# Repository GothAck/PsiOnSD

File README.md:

# PsiOnSD
## Brief
Building on the [Psioπ](https://hackaday.io/project/4042-psio) work by [RasmusB](https://hackaday.io/RasmusB), and utilizing the OSD3358 SiP,
I'm hoping to produce a drop in replacement for the Psion MX5 main board that will re-use the existing keyboard and display.

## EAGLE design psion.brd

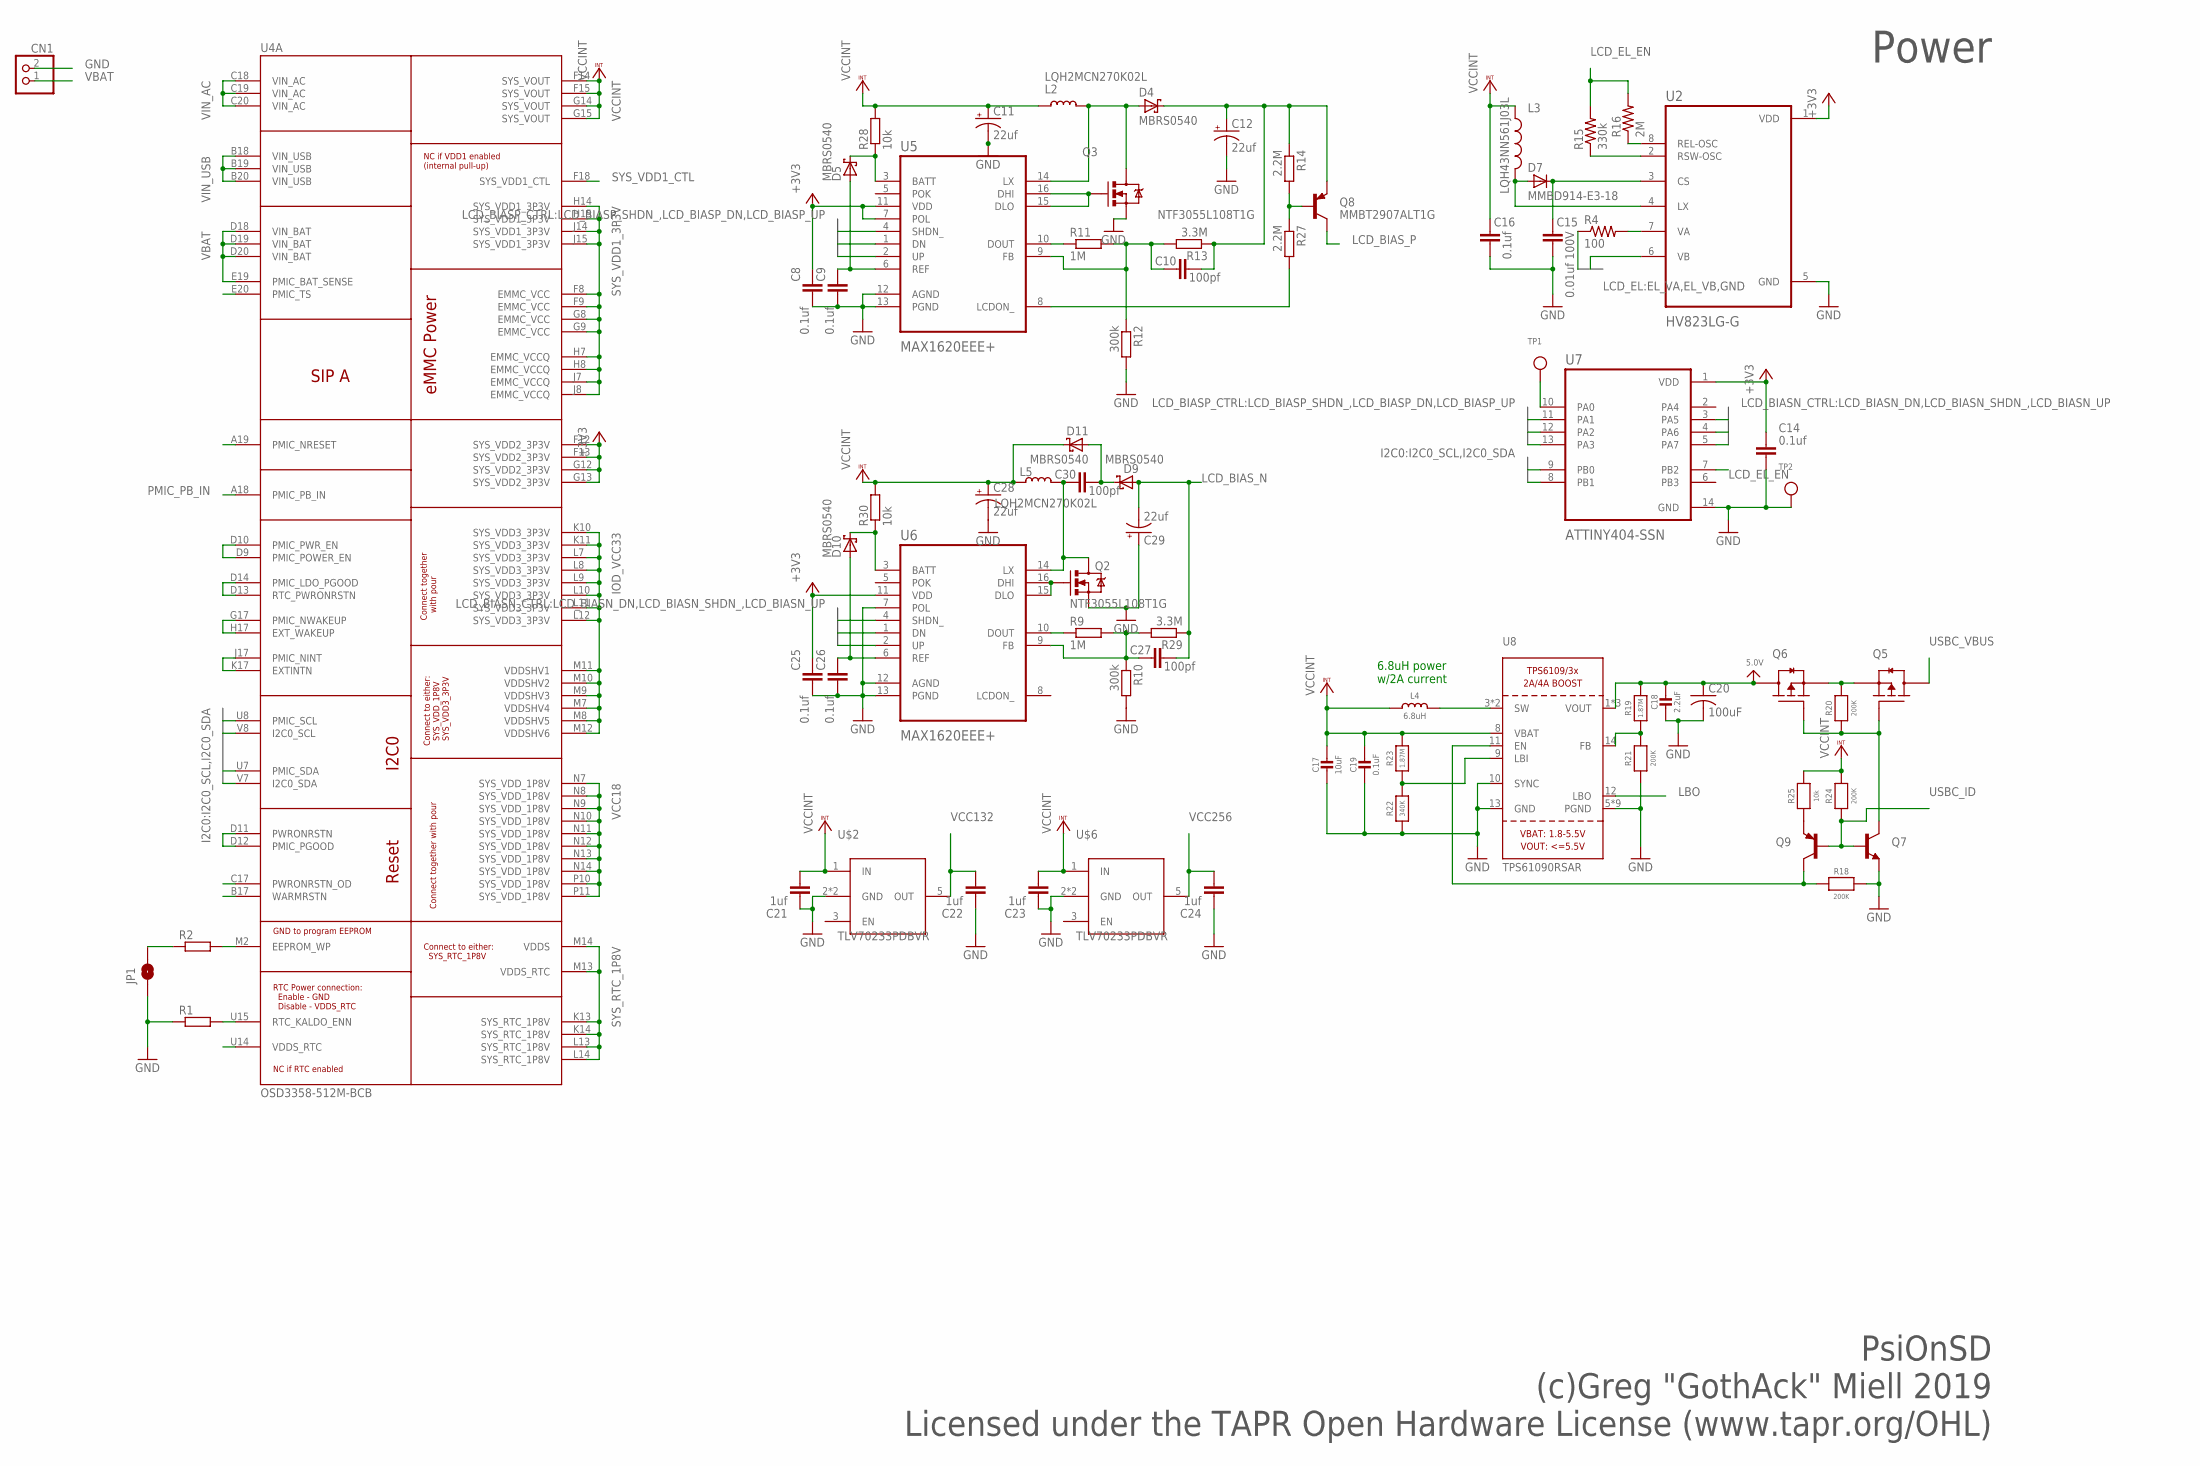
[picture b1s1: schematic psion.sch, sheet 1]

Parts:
C8, C9, C14, C16, C25, C26: 0.1uf; C805
C10, C27, C30: 100pf; C805
C11, C12, C28, C29: 22uf; CAPCP6032X280N
C15: 0.01uf 100V; C805
C17: 10uF; 0805
C18: 2.2uF; 0805
C19: 0.1uF; 0805
C20: 100uF; C1210
C21, C22, C23, C24: 1uf; C805
CN1: JST_2PIN-SMT-RA; JST-PH-2-SMT-RA
D4, D5, D9, D10, D11: MBRS0540; SOD3718X135N
D7: MMBD914-E3-18; SOT95P280X135-3N
JP1: JUMPER-SMT_2_NO_NO-SILK; SMT-JUMPER_2_NO_NO-SILK
L2, L5: LQH2MCN270K02L; INDUCTOR_1007
L3: LQH43NN561J03L; IND_LQH43CN1R0M03L
L4: 6.8uH; INDUCTOR_5X5MM_TDK_VLC5045
Q2, Q3: NTF3055L108T1G; SOT23-3
Q5, Q6: MOSFET-PCH_SOT-223; SOT230P700X160-4N
Q7: NPN_SOT-323; SOT65P210X110-3N
Q8: MMBT2907ALT1G; SOT95P280X135-3N
Q9: PNP_SOT-323; SOT65P210X110-3N
R1, R2: R-EU_R0805; R0805
R4: 100; M0805
R9, R11: 1M; R0805
R10, R12: 300k; R0805
R13, R29: 3.3M; R0805
R14, R27: 2.2M; R0805
R15: 330k; M0805
R16: 2M; M0805
R18, R20, R21, R24: 200K; 0805
R19: 1.87M; 0805
R22: 340K; _0805MP
R23: 1.87M; _0805MP
R25: 10k; 0805
R28, R30: 10k; R0805
TP1, TP2: TESTPOINTROUND1MM; TESTPOINT_ROUND_1MM
U2: HV823LG-G; SOIC127P600X175-8N
U4: OSD3358-512M-BCB; OSD335X-BGA-400
U5, U6: MAX1620EEE+; SOP63P602X175-16N
U7: ATTINY404-SSN; SOIC127P600X175-14N
U8: TPS61090RSAR; PVQFN-16
U$2, U$6: TLV70233PDBVR; SOT23-5

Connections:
5.0V: C18.1, C20.1, Q6.4 (D), R19.2, U8.1 (VOUT), U8.15 (VOUT), U8.16 (VOUT)
+3V3: C8.1, C14.1, C25.1, U2.1 (VDD), U4.F12 (SYS_VDD2_3P3V), U4.F13 (SYS_VDD2_3P3V), U4.G12 (SYS_VDD2_3P3V), U4.G13 (SYS_VDD2_3P3V), U5.7 (POL), U5.11 (VDD), U6.11 (VDD), U7.1 (VDD); also elsewhere on the board
BOOST_EN: Q9.3 (C), R18.1, U8.11 (EN)
EL_VA: R4.1; also elsewhere on the board
EL_VA_PRE: R4.2, U2.7 (VA)
EL_VB: U2.6 (VB); also elsewhere on the board
GND: C8.2, C9.2, C11.N (-), C12.N (-), C14.2, C15.2, C16.2, C17.2, C18.2, C19.2, C20.2, C21.1, C22.1, C23.1, C24.1, C25.2, C26.2, C28.N (-), C29.P (+), CN1.2 (1), JP1.1, Q2.2 (S), Q3.2 (S), Q7.2 (E), R1.1, R10.2, R12.2, R18.2, R21.1, R22.1, TP2.P$1, U2.5 (GND), U5.12 (AGND), U5.13 (PGND), U6.7 (POL), U6.12 (AGND), U6.13 (PGND), U7.14 (GND), U8.5 (PGND), U8.6 (PGND), U8.7 (PGND), U8.10 (SYNC), U8.13 (GND), U8.P$18 (PGND), U8.P$19 (PGND), U8.P$20 (PGND), U8.P$21 (PGND), U8.P$22 (PGND), U8.THERMAL (PGND), U$2.2 (GND), U$2.4 (GND), U$6.2 (GND), U$6.4 (GND); also elsewhere on the board
I2C0_SCL: U4.U8 (PMIC_SCL), U4.V8 (I2C0_SCL), U7.9 (PB0); also elsewhere on the board
I2C0_SDA: U4.U7 (PMIC_SDA), U4.V7 (I2C0_SDA), U7.8 (PB1); also elsewhere on the board
IOD_VCC33: U4.K10 (SYS_VDD3_3P3V), U4.K11 (SYS_VDD3_3P3V), U4.L7 (SYS_VDD3_3P3V), U4.L8 (SYS_VDD3_3P3V), U4.L9 (SYS_VDD3_3P3V), U4.L10 (SYS_VDD3_3P3V), U4.L11 (SYS_VDD3_3P3V), U4.L12 (SYS_VDD3_3P3V), U4.M7 (VDDSHV4), U4.M8 (VDDSHV5), U4.M9 (VDDSHV3), U4.M10 (VDDSHV2), U4.M11 (VDDSHV1), U4.M12 (VDDSHV6)
LBO: U8.12 (LBO)
LCD_BIASND_N: U6.1 (DN), U7.3 (PA5)
LCD_BIASN_SHDN_: U6.4 (SHDN_), U7.5 (PA7)
LCD_BIASN_UP: U6.2 (UP), U7.4 (PA6)
LCD_BIASPD_N: U5.1 (DN), U7.12 (PA2)
LCD_BIASP_SHDN_: U5.4 (SHDN_), U7.13 (PA3)
LCD_BIASP_UP: U5.2 (UP), U7.11 (PA1)
LCD_BIAS_N: C27.2, C29.N (-), D9.A, R29.1; also elsewhere on the board
LCD_BIAS_N_P1: C30.1, L5.P$2 (2), Q2.3 (D), U6.14 (LX)
LCD_BIAS_N_P2: C30.2, D9.K, D11.A
LCD_BIAS_P: Q8.3 (C); also elsewhere on the board
LCD_BIAS_P_P1: D4.A, L2.P$2 (2), Q3.3 (D), U5.14 (LX)
LCD_BIAS_P_P2: C10.2, C12.P (+), D4.K, Q8.2 (E), R13.1, R14.1
LCD_EL_EN: R15.2, R16.2, U7.7 (PB2)
unnamed: D7.1 (A), L3.2, U2.4 (LX)
unnamed: C15.1, D7.3 (K), U2.3 (CS)
unnamed: R2.2, U4.M2 (EEPROM_WP)
unnamed: U4.D9 (PMIC_POWER_EN), U4.D10 (PMIC_PWR_EN)
unnamed: U4.D13 (RTC_PWRONRSTN), U4.D14 (PMIC_LDO_PGOOD)
unnamed: U4.J17 (PMIC_NINT), U4.K17 (EXTINTN)
unnamed: U4.G17 (PMIC_NWAKEUP), U4.H17 (EXT_WAKEUP)
unnamed: U4.D11 (PWRONRSTN), U4.D12 (PMIC_PGOOD)
unnamed: JP1.2, R2.1
unnamed: Q3.1 (G), U5.15 (DLO), U5.16 (DHI)
unnamed: Q2.1 (G), U6.15 (DLO), U6.16 (DHI)
unnamed: R11.1, U5.10 (DOUT)
unnamed: C10.1, R11.2, R12.1, R13.2, U5.9 (FB)
unnamed: Q8.1 (B), R14.2, R27.1
unnamed: TP1.P$1, U7.10 (PA0)
unnamed: R27.2, U5.8 (LCDON_)
unnamed: R15.1, U2.2 (RSW-OSC)
unnamed: R16.1, U2.8 (REL-OSC)
unnamed: R22.2, R23.1, U8.9 (LBI)
unnamed: R19.1, R21.2, U8.14 (FB)
unnamed: Q5.1 (G), Q6.1 (G), Q7.3 (C), R20.1
unnamed: Q9.2 (E), R25.1
unnamed: D5.K, R28.1, U5.3 (BATT)
unnamed: C9.1, D5.A, U5.6 (REF)
unnamed: R9.1, U6.10 (DOUT)
unnamed: C27.1, R9.2, R10.1, R29.2, U6.9 (FB)
unnamed: D10.K, R30.1, U6.3 (BATT)
unnamed: C26.1, D10.A, U6.6 (REF)
PMIC_NRESET: U4.A19 (PMIC_NRESET)
PMIC_PB_IN: U4.A18 (PMIC_PB_IN); also elsewhere on the board
PMIC_TS: U4.E20 (PMIC_TS)
PWRONRSTN_OD: U4.C17 (PWRONRSTN_OD)
ROPU: R1.2, U4.U15 (RTC_KALDO_ENN)
SYS_RTC_1P8V: U4.K13 (SYS_RTC_1P8V), U4.K14 (SYS_RTC_1P8V), U4.L13 (SYS_RTC_1P8V), U4.L14 (SYS_RTC_1P8V), U4.M13 (VDDS_RTC), U4.M14 (VDDS)
SYS_VDD1_3P3V: U4.F8 (EMMC_VCC), U4.F9 (EMMC_VCC), U4.G8 (EMMC_VCC), U4.G9 (EMMC_VCC), U4.H7 (EMMC_VCCQ), U4.H8 (EMMC_VCCQ), U4.H14 (SYS_VDD1_3P3V), U4.H15 (SYS_VDD1_3P3V), U4.J7 (EMMC_VCCQ), U4.J8 (EMMC_VCCQ), U4.J14 (SYS_VDD1_3P3V), U4.J15 (SYS_VDD1_3P3V)
SYS_VDD1_CTL: U4.F18 (SYS_VDD1_CTL)
USBC_ID: Q7.1 (B), Q9.1 (B), R24.1; also elsewhere on the board
USBC_IND_SW: L4.P$2 (2), U8.3 (SW), U8.4 (SW)
USBC_VBUS: Q5.4 (D); also elsewhere on the board
USBC_VBUS_SW: Q5.3 (S), Q6.3 (S), R20.2
VBAT: CN1.1 (2), U4.D18 (VIN_BAT), U4.D19 (VIN_BAT), U4.D20 (VIN_BAT), U4.E19 (PMIC_BAT_SENSE); also elsewhere on the board
VCC18: U4.N7 (SYS_VDD_1P8V), U4.N8 (SYS_VDD_1P8V), U4.N9 (SYS_VDD_1P8V), U4.N10 (SYS_VDD_1P8V), U4.N11 (SYS_VDD_1P8V), U4.N12 (SYS_VDD_1P8V), U4.N13 (SYS_VDD_1P8V), U4.N14 (SYS_VDD_1P8V), U4.P10 (SYS_VDD_1P8V), U4.P11 (SYS_VDD_1P8V)
VCC132: C22.2, U$2.5 (OUT); also elsewhere on the board
VCC256: C24.2, U$6.5 (OUT); also elsewhere on the board
VCCINT: C11.P (+), C16.1, C17.1, C19.1, C21.2, C23.2, C28.P (+), D11.K, L2.P$1 (1), L3.1, L4.P$1 (1), L5.P$1 (1), R23.2, R24.2, R25.2, R28.2, R30.2, U4.F14 (SYS_VOUT), U4.F15 (SYS_VOUT), U4.G14 (SYS_VOUT), U4.G15 (SYS_VOUT), U8.8 (VBAT), U$2.1 (IN), U$6.1 (IN); also elsewhere on the board
VDDS_RTC@2: U4.U14 (VDDS_RTC)
VIN_AC: U4.C18 (VIN_AC), U4.C19 (VIN_AC), U4.C20 (VIN_AC)
VIN_USB: U4.B18 (VIN_USB), U4.B19 (VIN_USB), U4.B20 (VIN_USB)
WARMRSTN: U4.B17 (WARMRSTN)

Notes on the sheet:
PsiOnSD (c)Greg "GothAck" Miell 2019 Licensed under the TAPR Open Hardware License (www.tapr.org/OHL)
Power
6.8uH power w/2A current

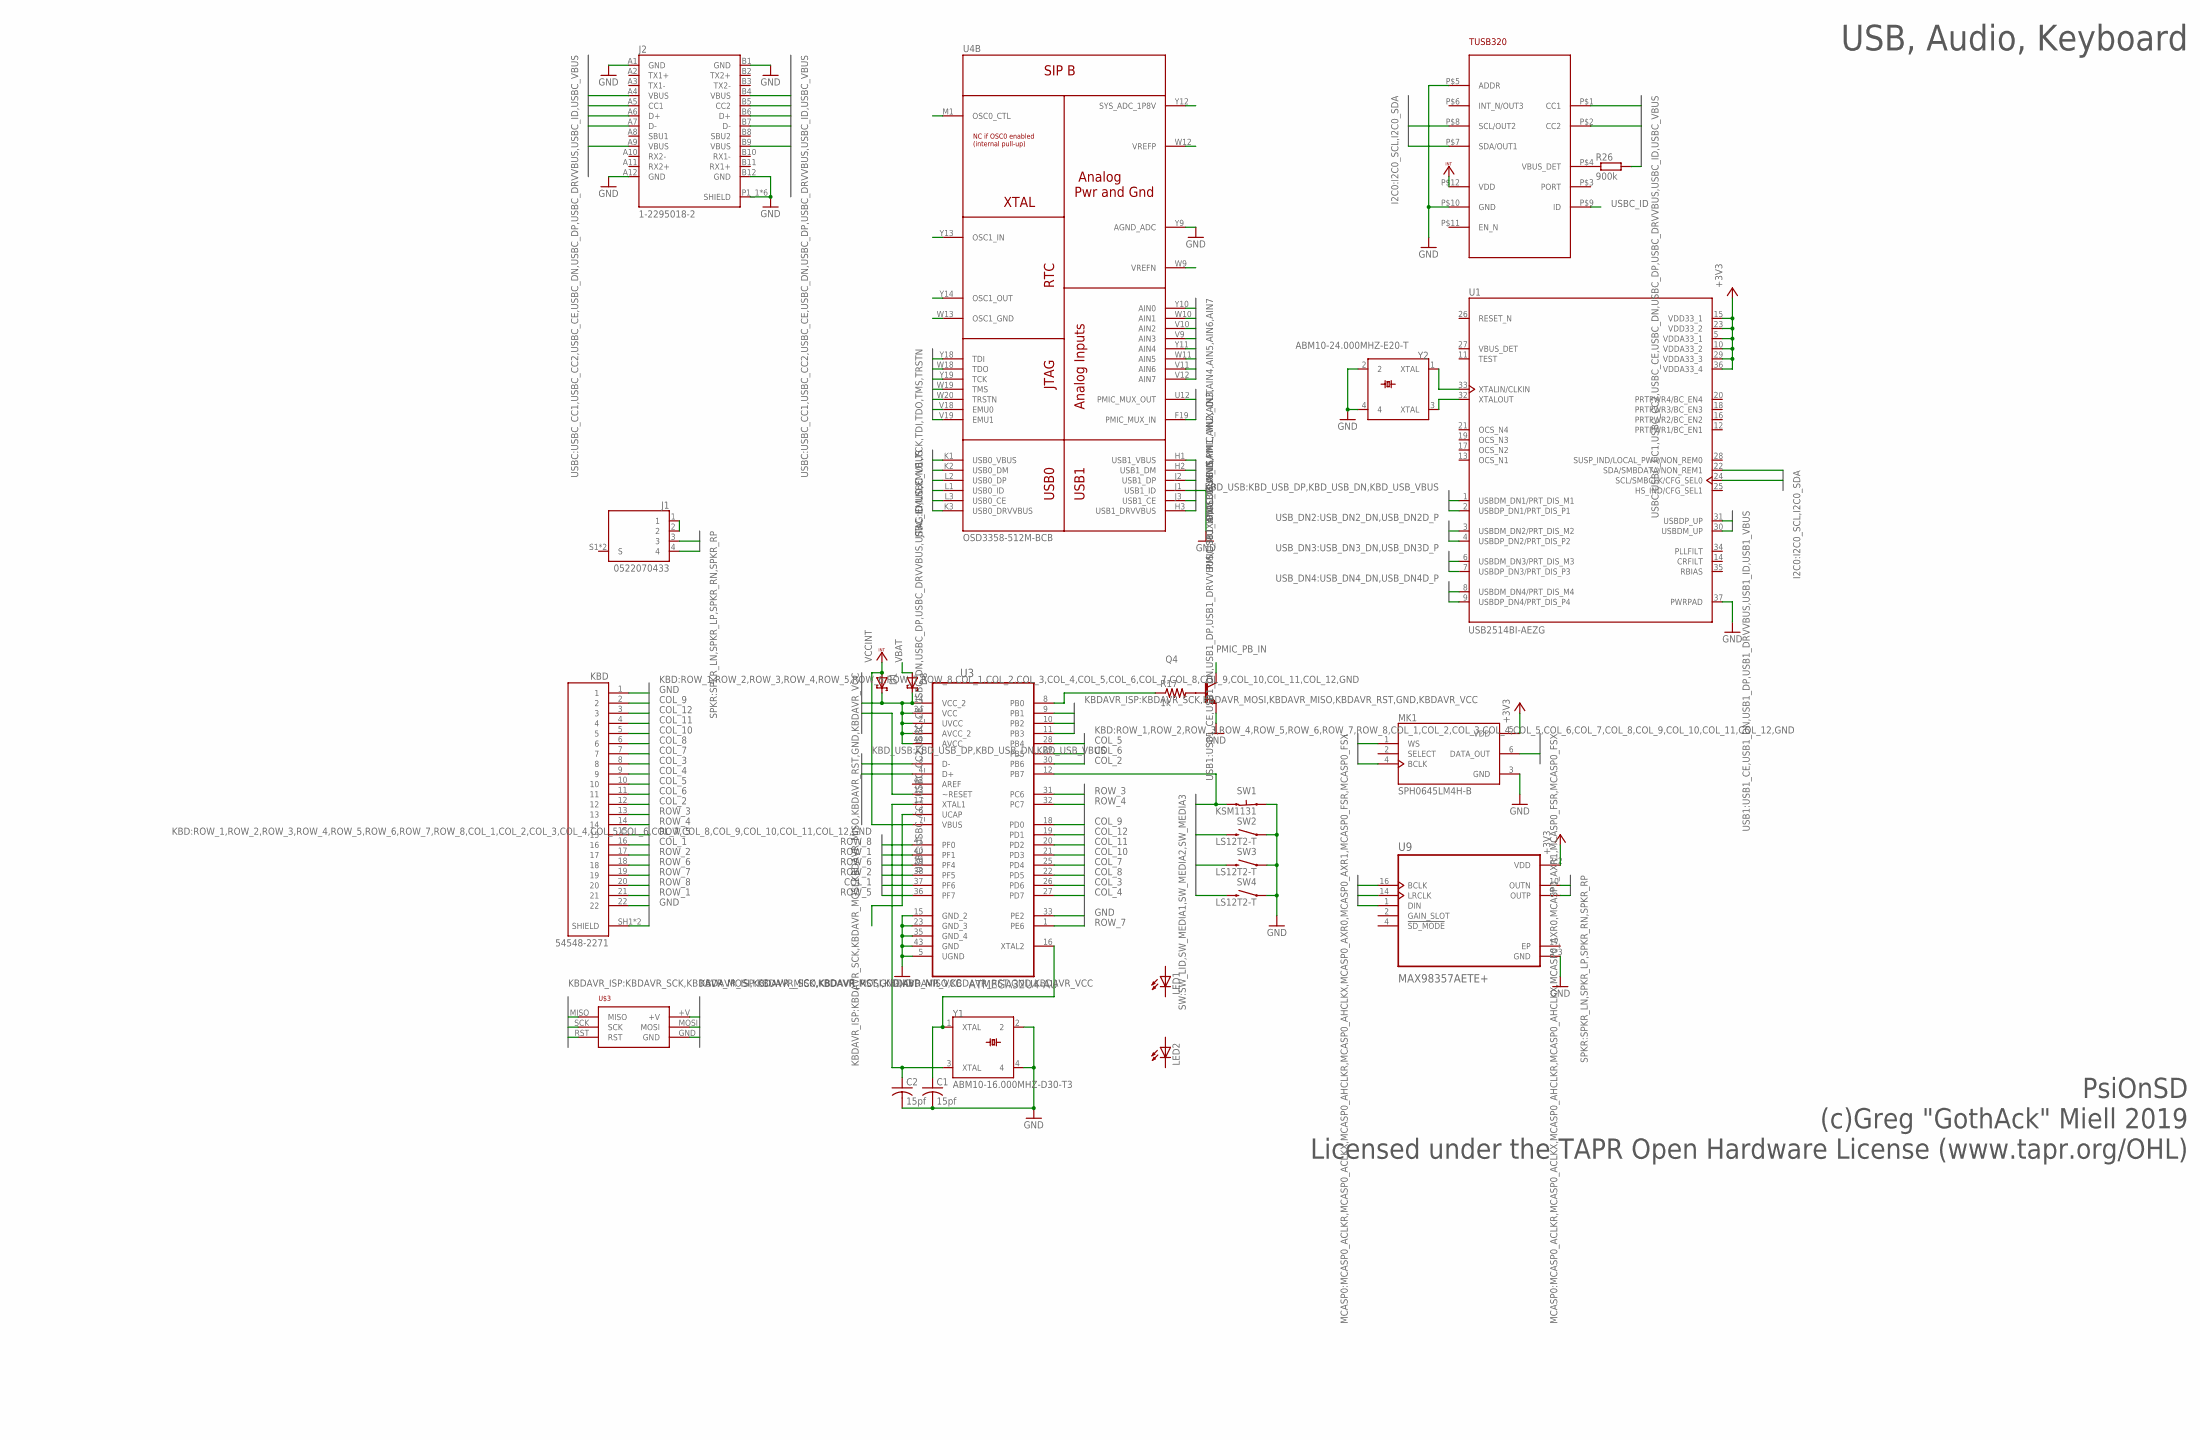
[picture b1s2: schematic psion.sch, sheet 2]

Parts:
C1, C2: 15pf; C0402
D1, D8: SCHOTTKY_SOD-123; SOD3718X135N
J1: 0522070433; MOLEX_0522070433
J2: 1-2295018-2; TE_1-2295018-2
KBD: 54548-2271; MOLEX_54548-2271
LED1, LED2: LEDCHIP-LED0805; CHIP-LED0805
MK1: SPH0645LM4H-B; MIC_SPH0645LM4H-B
Q4: NPN_SOT-323; SOT65P210X110-3N
R17: 1k; M0805
R26: 900k; R0805
SW1: KSM1131
SW2, SW3, SW4: LS12T2-T
U1: USB2514BI-AEZG; QFN50P600X600X100-37N
U3: ATMEGA32U4-AU; QFP80P1200X1200X120-44N
U4: OSD3358-512M-BCB; OSD335X-BGA-400
U9: MAX98357AETE+; QFN50P300X300X80-17N
U$3: 1.27MM-ICSP
U$4: TUSB320XQFN; X2QFN
Y1: ABM10-16.000MHZ-D30-T3; XTAL250X200X50
Y2: ABM10-24.000MHZ-E20-T; XTAL250X200X50

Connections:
+3V3: MK1.5 (VDD), U1.5 (VDDA33_1), U1.10 (VDDA33_2), U1.15 (VDD33_1), U1.23 (VDD33_2), U1.29 (VDDA33_3), U1.36 (VDDA33_4), U9.7 (VDD), U9.8 (VDD); also elsewhere on the board
AIN0: U4.Y10 (AIN0)
AIN1: U4.W10 (AIN1)
AIN2: U4.V10 (AIN2)
AIN3: U4.V9 (AIN3)
AIN4: U4.Y11 (AIN4)
AIN5: U4.W11 (AIN5)
AIN6: U4.V11 (AIN6)
AIN7: U4.V12 (AIN7)
COL_1: KBD.16, U3.37 (PF6)
COL_2: KBD.12, U3.30 (PB6)
COL_3: KBD.8, U3.26 (PD6)
COL_4: KBD.9, U3.27 (PD7)
COL_5: KBD.10, U3.28 (PB4)
COL_6: KBD.11, U3.29 (PB5)
COL_7: KBD.7, U3.25 (PD4)
COL_8: KBD.6, U3.22 (PD5)
COL_9: KBD.2, U3.18 (PD0)
COL_10: KBD.5, U3.21 (PD3)
COL_11: KBD.4, U3.20 (PD2)
COL_12: KBD.3, U3.19 (PD1)
EMU0: U4.V18 (EMU0)
EMU1: U4.V19 (EMU1)
EP: U9.17 (EP)
GND: C1.2, C2.2, J2.A1 (GND), J2.A12 (GND), J2.B1 (GND), J2.B12 (GND), J2.P1_1 (SHIELD), J2.P1_2 (SHIELD), J2.P2_1 (SHIELD), J2.P2_2 (SHIELD), J2.P4 (SHIELD), J2.P5 (SHIELD), KBD.1, KBD.22, KBD.SH1 (SHIELD), KBD.SH2 (SHIELD), MK1.3 (GND), Q4.2 (E), SW1.1, SW2.1, SW3.1, SW4.1, U1.37 (PWRPAD), U3.5 (UGND), U3.15 (GND_2), U3.23 (GND_3), U3.33 (PE2), U3.35 (GND_4), U3.43 (GND), U4.J1 (USB1_ID), U4.Y9 (AGND_ADC), U9.3 (GND), U9.11 (GND), U9.15 (GND), U$3.GND, U$4.P$5 (ADDR), U$4.P$10 (GND), Y1.2, Y1.4, Y2.2, Y2.4; also elsewhere on the board
I2C0_SCL: U1.24 (SCL/SMBCLK/CFG_SEL0), U$4.P$8 (SCL/OUT2); also elsewhere on the board
I2C0_SDA: U1.22 (SDA/SMBDATA/NON_REM1), U$4.P$7 (SDA/OUT1); also elsewhere on the board
KBDAVR_MISO: U3.11 (PB3), U$3.MISO
KBDAVR_MOSI: U3.10 (PB2), U$3.MOSI
KBDAVR_RST: U3.13 (~RESET), U$3.RST
KBDAVR_SCK: U3.9 (PB1), U$3.SCK
KBDAVR_VCC: D1.K, D8.K, U3.2 (UVCC), U3.14 (VCC_2), U3.24 (AVCC_2), U3.34 (VCC), U3.44 (AVCC), U$3.+V
KBD_USBD_N: U1.1 (USBDM_DN1/PRT_DIS_M1), U3.3 (D-)
KBD_USBD_P: U1.2 (USBDP_DN1/PRT_DIS_P1), U3.4 (D+)
MCASP0_ACLKR: MK1.4 (BCLK); also elsewhere on the board
MCASP0_ACLKX: U9.16 (BCLK); also elsewhere on the board
MCASP0_AXR0: U9.1 (DIN); also elsewhere on the board
MCASP0_AXR1: MK1.6 (DATA_OUT); also elsewhere on the board
MCASP0_FSR: MK1.1 (WS); also elsewhere on the board
MCASP0_FSX: U9.14 (LRCLK); also elsewhere on the board
unnamed: U1.33 (XTALIN/CLKIN), Y2.1 (XTAL)
unnamed: C1.1, U3.16 (XTAL2), Y1.1 (XTAL)
unnamed: C2.1, U3.17 (XTAL1), Y1.3 (XTAL)
unnamed: U1.32 (XTALOUT), Y2.3 (XTAL)
unnamed: J1.1, J1.2
unnamed: R17.1, U3.8 (PB0)
unnamed: Q4.1 (B), R17.2
unnamed: R26.1, U$4.P$4 (VBUS_DET)
OSC0_CTL: U4.M1 (OSC0_CTL)
OSC1_GND: U4.W13 (OSC1_GND)
OSC1_IN: U4.Y13 (OSC1_IN)
OSC1_OUT: U4.Y14 (OSC1_OUT)
PMIC_MUX_IN: U4.F19 (PMIC_MUX_IN)
PMIC_MUX_OUT: U4.U12 (PMIC_MUX_OUT)
PMIC_PB_IN: Q4.3 (C); also elsewhere on the board
ROW_1: KBD.21, U3.40 (PF1)
ROW_2: KBD.17, U3.38 (PF5)
ROW_3: KBD.13, U3.31 (PC6)
ROW_4: KBD.14, U3.32 (PC7)
ROW_5: KBD.15, U3.36 (PF7)
ROW_6: KBD.18, U3.39 (PF4)
ROW_7: KBD.19, U3.1 (PE6)
ROW_8: KBD.20, U3.41 (PF0)
S: J1.S1 (S), J1.S2 (S)
SPKR_LN: J1.3, U9.10 (OUTN)
SPKR_LP: J1.4, U9.9 (OUTP)
SW_LID: SW1.2, U3.12 (PB7)
SW_MEDIA1: SW2.2
SW_MEDIA2: SW3.2
SW_MEDIA3: SW4.2
SYS_ADC_1P8V: U4.Y12 (SYS_ADC_1P8V)
TCK: U4.Y19 (TCK)
TDI: U4.Y18 (TDI)
TDO: U4.W18 (TDO)
TMS: U4.W19 (TMS)
TRSTN: U4.W20 (TRSTN)
USB1D_N: U1.30 (USBDM_UP), U4.H2 (USB1_DM)
USB1D_P: U1.31 (USBDP_UP), U4.J2 (USB1_DP)
USB1_CE: U4.J3 (USB1_CE)
USB1_DRVVBUS: U4.H3 (USB1_DRVVBUS)
USB1_VBUS: U4.H1 (USB1_VBUS)
USBCD_N: J2.A7 (D-), J2.B7 (D-), U4.K2 (USB0_DM)
USBCD_P: J2.A6 (D+), J2.B6 (D+), U4.L2 (USB0_DP)
USBC_CC1: J2.A5 (CC1), U$4.P$1 (CC1)
USBC_CC2: J2.B5 (CC2), U$4.P$2 (CC2)
USBC_CE: U4.L3 (USB0_CE)
USBC_DRVVBUS: U4.K3 (USB0_DRVVBUS)
USBC_ID: U4.L1 (USB0_ID), U$4.P$9 (ID); also elsewhere on the board
USBC_VBUS: J2.A4 (VBUS), J2.A9 (VBUS), J2.B4 (VBUS), J2.B9 (VBUS), R26.2, U4.K1 (USB0_VBUS); also elsewhere on the board
USB_DN2D_N: U1.3 (USBDM_DN2/PRT_DIS_M2)
USB_DN2D_P: U1.4 (USBDP_DN2/PRT_DIS_P2)
USB_DN3D_N: U1.6 (USBDM_DN3/PRT_DIS_M3)
USB_DN3D_P: U1.7 (USBDP_DN3/PRT_DIS_P3)
USB_DN4D_N: U1.8 (USBDM_DN4/PRT_DIS_M4)
USB_DN4D_P: U1.9 (USBDP_DN4/PRT_DIS_P4)
VBAT: D8.A; also elsewhere on the board
VCCINT: D1.A, U3.7 (VBUS), U$4.P$12 (VDD); also elsewhere on the board
VREFN: U4.W9 (VREFN)
VREFP: U4.W12 (VREFP)

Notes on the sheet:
PsiOnSD (c)Greg "GothAck" Miell 2019 Licensed under the TAPR Open Hardware License (www.tapr.org/OHL)
USB, Audio, Keyboard

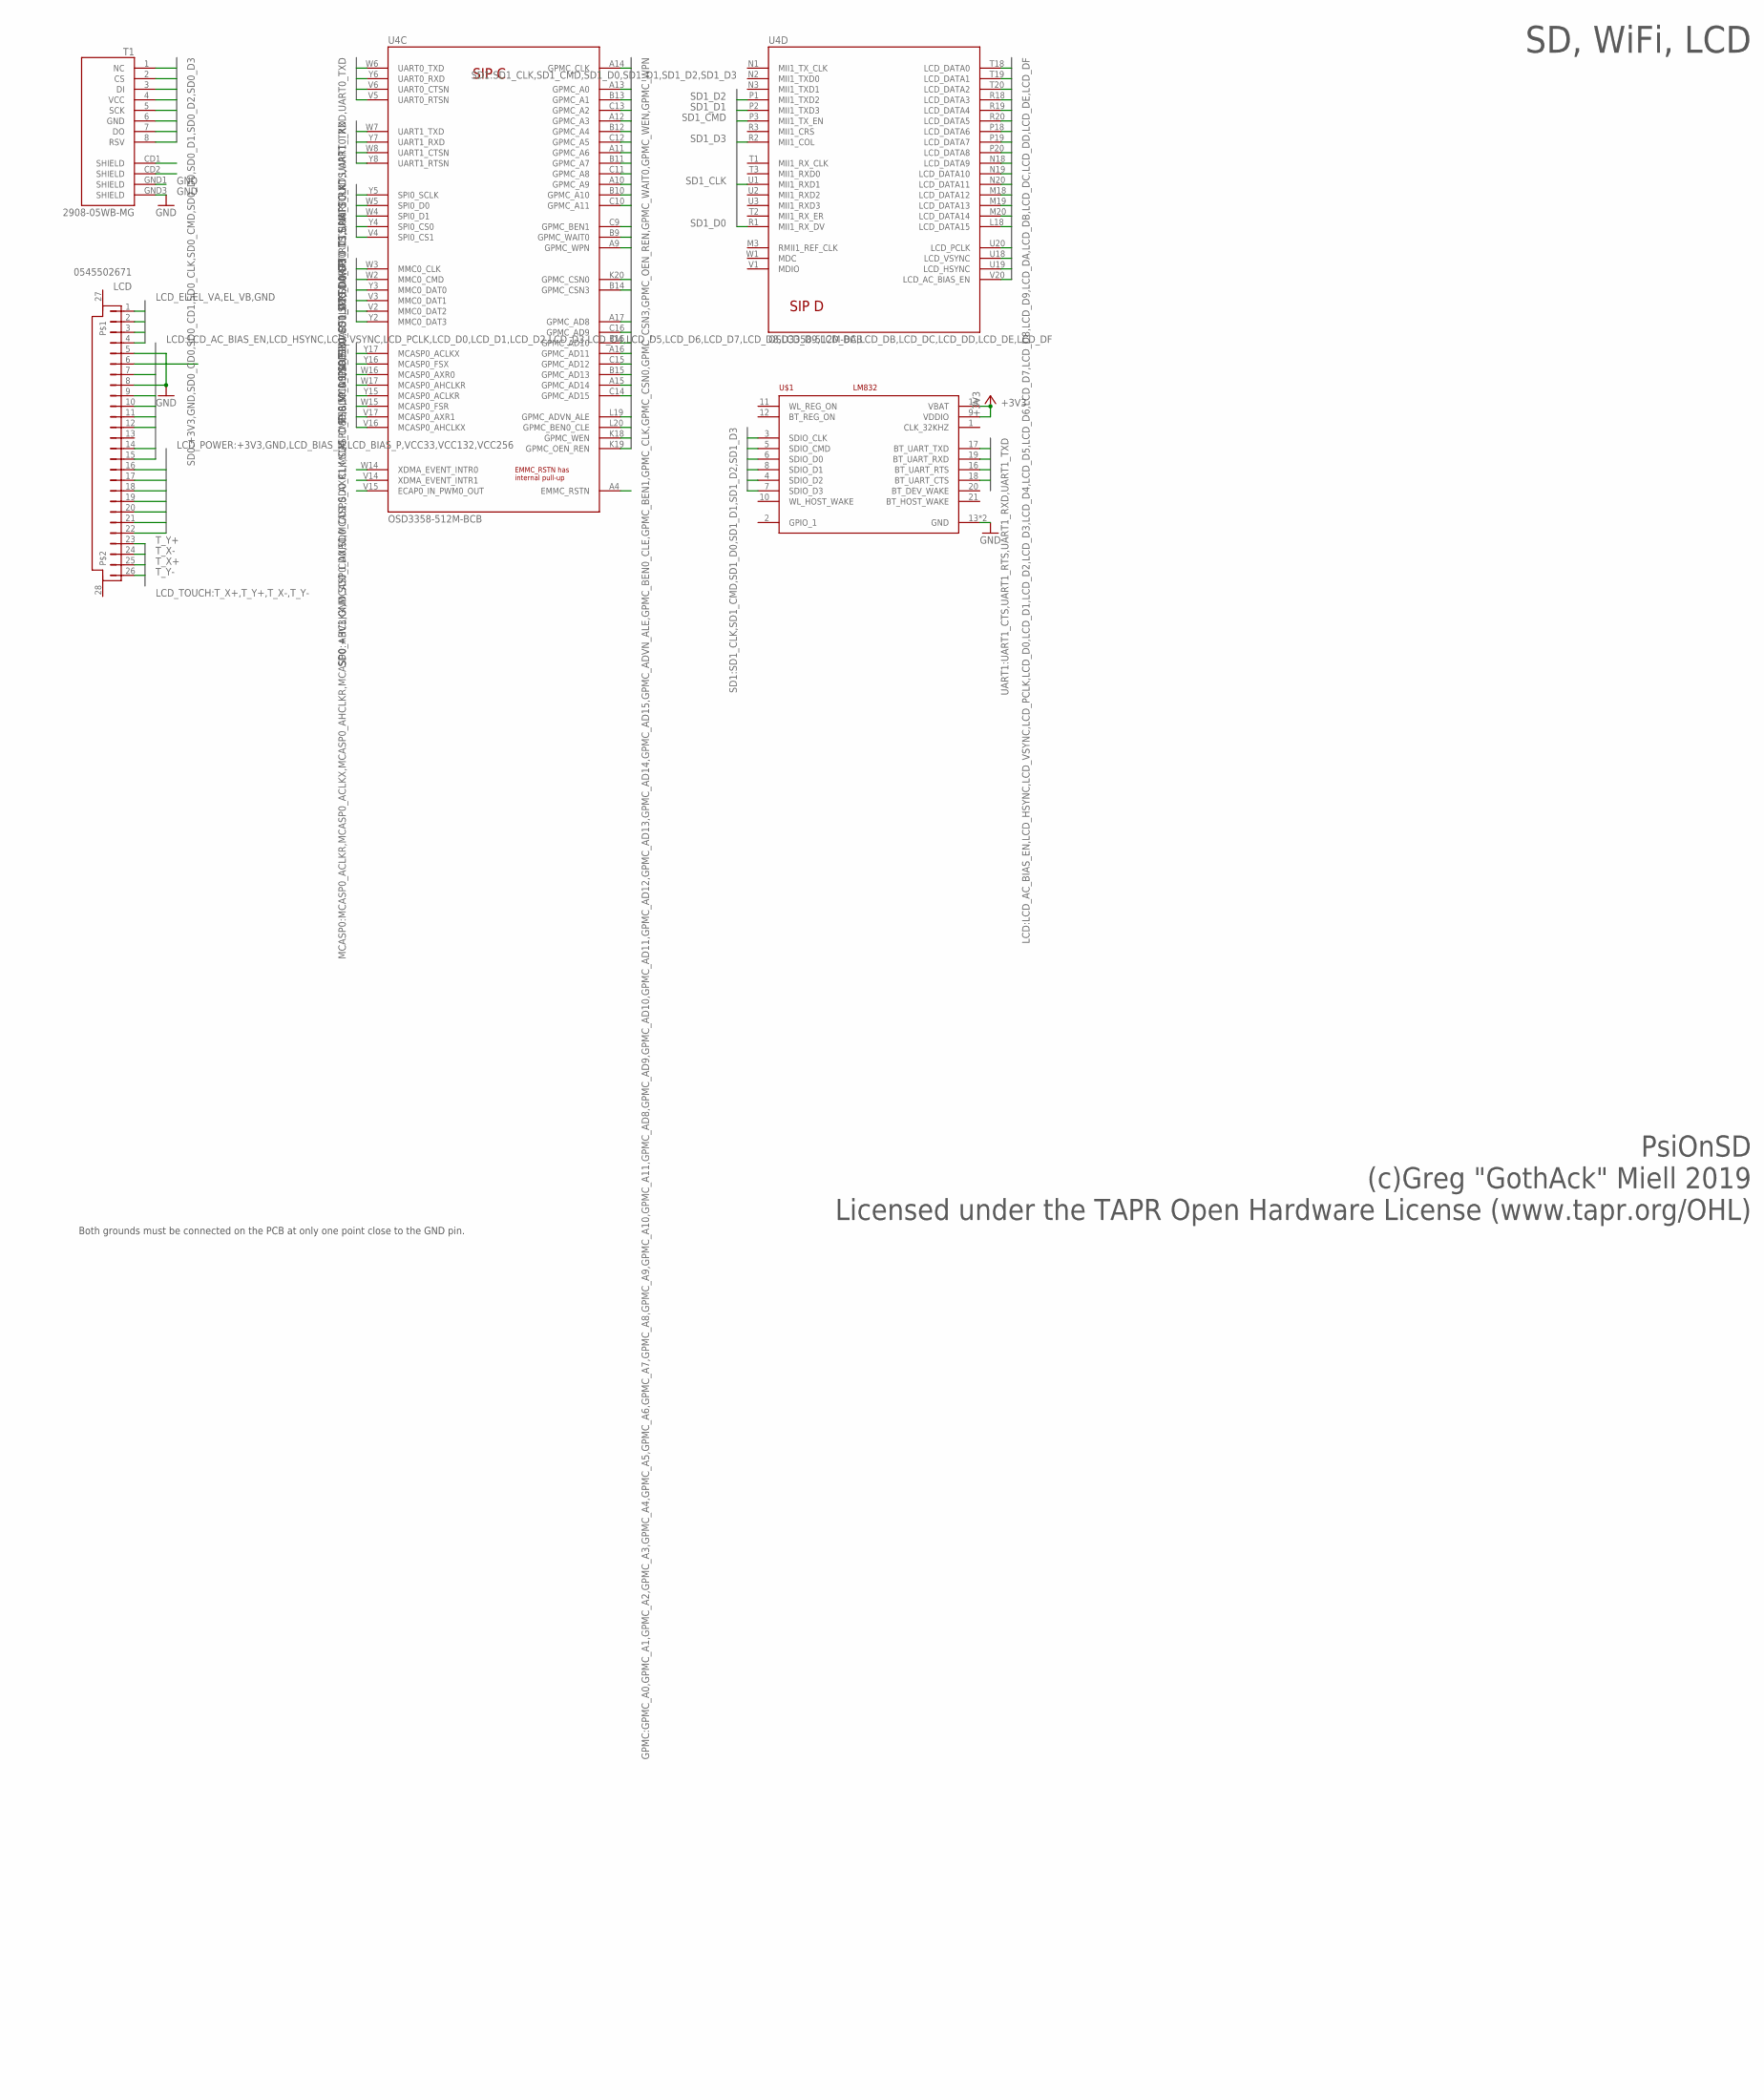
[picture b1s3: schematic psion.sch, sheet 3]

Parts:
LCD: 0545502671
T1: 2908-05WB-MG; MICRO-SD-SOCKET-PP
U4: OSD3358-512M-BCB; OSD335X-BGA-400
U$1: LM832EMBEDDED; LM832SMT_EMB

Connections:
+3V3: LCD.16, LCD.21, T1.4 (VCC), U$1.9 (VDDIO), U$1.14 (VBAT); also elsewhere on the board
ECAP0_IN_PWM0_OUT: U4.V15 (ECAP0_IN_PWM0_OUT)
EL_VA: LCD.3; also elsewhere on the board
EL_VB: LCD.1; also elsewhere on the board
EMMC_RSTN: U4.A4 (EMMC_RSTN)
GND: LCD.2, LCD.4, LCD.5, LCD.8, LCD.22, T1.6 (GND), T1.GND1 (SHIELD), T1.GND3 (SHIELD), U$1.13 (GND), U$1.15 (GND); also elsewhere on the board
GPMC_A0: U4.A13 (GPMC_A0)
GPMC_A1: U4.B13 (GPMC_A1)
GPMC_A2: U4.C13 (GPMC_A2)
GPMC_A3: U4.A12 (GPMC_A3)
GPMC_A4: U4.B12 (GPMC_A4)
GPMC_A5: U4.C12 (GPMC_A5)
GPMC_A6: U4.A11 (GPMC_A6)
GPMC_A7: U4.B11 (GPMC_A7)
GPMC_A8: U4.C11 (GPMC_A8)
GPMC_A9: U4.A10 (GPMC_A9)
GPMC_A10: U4.B10 (GPMC_A10)
GPMC_A11: U4.C10 (GPMC_A11)
GPMC_AD8: U4.A17 (GPMC_AD8)
GPMC_AD9: U4.C16 (GPMC_AD9)
GPMC_AD10: U4.B16 (GPMC_AD10)
GPMC_AD11: U4.A16 (GPMC_AD11)
GPMC_AD12: U4.C15 (GPMC_AD12)
GPMC_AD13: U4.B15 (GPMC_AD13)
GPMC_AD14: U4.A15 (GPMC_AD14)
GPMC_AD15: U4.C14 (GPMC_AD15)
GPMC_ADVN_ALE: U4.L19 (GPMC_ADVN_ALE)
GPMC_BEN0_CLE: U4.L20 (GPMC_BEN0_CLE)
GPMC_BEN1: U4.C9 (GPMC_BEN1)
GPMC_CLK: U4.A14 (GPMC_CLK)
GPMC_CSN0: U4.K20 (GPMC_CSN0)
GPMC_CSN3: U4.B14 (GPMC_CSN3)
GPMC_OEN_REN: U4.K19 (GPMC_OEN_REN)
GPMC_WAIT0: U4.B9 (GPMC_WAIT0)
GPMC_WEN: U4.K18 (GPMC_WEN)
GPMC_WPN: U4.A9 (GPMC_WPN)
LCD_AC_BIAS_EN: U4.V20 (LCD_AC_BIAS_EN)
LCD_BIAS_N: LCD.19; also elsewhere on the board
LCD_BIAS_P: LCD.20; also elsewhere on the board
LCD_D0: LCD.12, U4.T18 (LCD_DATA0)
LCD_D1: LCD.11, U4.T19 (LCD_DATA1)
LCD_D2: LCD.10, U4.T20 (LCD_DATA2)
LCD_D3: LCD.9, U4.R18 (LCD_DATA3)
LCD_D4: U4.R19 (LCD_DATA4)
LCD_D5: U4.R20 (LCD_DATA5)
LCD_D6: U4.P18 (LCD_DATA6)
LCD_D7: U4.P19 (LCD_DATA7)
LCD_D8: U4.P20 (LCD_DATA8)
LCD_D9: U4.N18 (LCD_DATA9)
LCD_DA: U4.N19 (LCD_DATA10)
LCD_DB: U4.N20 (LCD_DATA11)
LCD_DC: U4.M18 (LCD_DATA12)
LCD_DD: U4.M19 (LCD_DATA13)
LCD_DE: U4.M20 (LCD_DATA14)
LCD_DF: U4.L18 (LCD_DATA15)
LCD_HSYNC: LCD.15, U4.U19 (LCD_HSYNC)
LCD_PCLK: LCD.14, U4.U20 (LCD_PCLK)
LCD_VSYNC: LCD.7, U4.U18 (LCD_VSYNC)
MCASP0_ACLKR: U4.Y15 (MCASP0_ACLKR); also elsewhere on the board
MCASP0_ACLKX: U4.Y17 (MCASP0_ACLKX); also elsewhere on the board
MCASP0_AHCLKR: U4.W17 (MCASP0_AHCLKR)
MCASP0_AHCLKX: U4.V16 (MCASP0_AHCLKX)
MCASP0_AXR0: U4.W16 (MCASP0_AXR0); also elsewhere on the board
MCASP0_AXR1: U4.V17 (MCASP0_AXR1); also elsewhere on the board
MCASP0_FSR: U4.W15 (MCASP0_FSR); also elsewhere on the board
MCASP0_FSX: U4.Y16 (MCASP0_FSX); also elsewhere on the board
SD0_CD0: T1.CD1 (SHIELD)
SD0_CD1: T1.CD2 (SHIELD)
SD0_CLK: T1.5 (SCK), U4.W3 (MMC0_CLK)
SD0_CMD: T1.3 (DI), U4.W2 (MMC0_CMD)
SD0_D0: T1.7 (DO), U4.Y3 (MMC0_DAT0)
SD0_D1: T1.8 (RSV), U4.V3 (MMC0_DAT1)
SD0_D2: T1.1 (NC), U4.V2 (MMC0_DAT2)
SD0_D3: T1.2 (CS), U4.Y2 (MMC0_DAT3)
SD1_CLK: U4.U1 (MII1_RXD1), U$1.3 (SDIO_CLK)
SD1_CMD: U4.P3 (MII1_TX_EN), U$1.5 (SDIO_CMD)
SD1_D0: U4.R1 (MII1_RX_DV), U$1.6 (SDIO_D0)
SD1_D1: U4.P2 (MII1_TXD3), U$1.8 (SDIO_D1)
SD1_D2: U4.P1 (MII1_TXD2), U$1.4 (SDIO_D2)
SD1_D3: U4.R2 (MII1_COL), U$1.7 (SDIO_D3)
SPI0_CS0: U4.Y4 (SPI0_CS0)
SPI0_CS1: U4.V4 (SPI0_CS1)
SPI0_D0: U4.W5 (SPI0_D0)
SPI0_D1: U4.W4 (SPI0_D1)
SPI0_SCLK: U4.Y5 (SPI0_SCLK)
T_X+: LCD.25
T_X-: LCD.24
T_Y+: LCD.23
T_Y-: LCD.26
UART0_CTS: U4.V6 (UART0_CTSN)
UART0_RTS: U4.V5 (UART0_RTSN)
UART0_RXD: U4.Y6 (UART0_RXD)
UART0_TXD: U4.W6 (UART0_TXD)
UART1_CTS: U4.W8 (UART1_CTSN), U$1.18 (BT_UART_CTS)
UART1_RTS: U4.Y8 (UART1_RTSN), U$1.16 (BT_UART_RTS)
UART1_RXD: U4.Y7 (UART1_RXD), U$1.17 (BT_UART_TXD)
UART1_TXD: U4.W7 (UART1_TXD), U$1.19 (BT_UART_RXD)
VCC132: LCD.17; also elsewhere on the board
VCC256: LCD.18; also elsewhere on the board
XDMA_EVENT_INTR0: U4.W14 (XDMA_EVENT_INTR0)
XDMA_EVENT_INTR1: U4.V14 (XDMA_EVENT_INTR1)

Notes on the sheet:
Both grounds must be connected on the PCB at only one point close to the GND pin.
PsiOnSD (c)Greg "GothAck" Miell 2019 Licensed under the TAPR Open Hardware License (www.tapr.org/OHL)
SD, WiFi, LCD

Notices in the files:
parts and their libraries:
microbuilder: This work is placed in the public domain, and may be freely used for commercial and non-commercial work with the following conditions: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
SparkFun-Jumpers: Licensing: Creative Commons ShareAlike 4.0 International - https://creativecommons.org/licenses/by-sa/4.0
